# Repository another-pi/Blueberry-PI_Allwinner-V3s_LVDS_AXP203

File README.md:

main build board now is `Blueberry Pi 7.1.2.esp32.no-lan.gsm-a9g`. because `a9g` gsm module is much better then `sim800c`. because of open source SDK and support of GPS.

but still work-in-progress. not finished.

sources of Linux kernel (4.10.15) for this board(s). preconfigured:
https://github.com/bhgv/linux

precompiled Linux-4.10.15 SD-image with support of fb-graphics an resistive touch:
https://github.com/bhgv/linux/releases/tag/1.0a

Blueberry Pi 7.1.2.esp32.no-lan
===============================
(not finished yet)
* removed lan port,
* added 50pins fpc RGB connector for popular 7" tfts (AT070TN[90, 91, 92, 93, 94]) in parallel to 40pins one,
* connector for capacitive touchscreens (i2c1),
* power converters for 50pins socket,
* 25% smaller board.
* esp32 now wired as wifi/bluetooth and as io expander-coprocessor.

Blueberry Pi 7.1.1+ESP32-S
==========================
(not finised yet)
* other power controller(s). 3 cheap and easy to solder chips in sot23-6,
* a try to use ESP32-S module as a WiFi/Bluetooth co-processor.

List of compatible (and cheap) LCDs (with touchscreens)
=======================================================
* ? 7" -- MDT7000
* 7" -- TKR7040B
* 7" -- GL070009T0-40

* 6" -- KD060G1-40nc-a5
* 6" -- TM060RDH02

* 5" -- HSD050IDW1-A20
* 5" -- MH0506D
* 5" -- KD50G21-40NT-A1
* 5" -- A26TF9C032169 * A0 -A20
* 5" -- H-H050L-12M
* 5" -- GL050001C0-40
* 5" -- ft050s800480005n-v01
* 5" -- HW800480F-0F-0L-20
* 5" -- hw800480f-0f-0l-10
* 5" -- T050SWV012T
* 5" -- T050SWV015T
* 5" -- FC050S151-01
* 5" -- KD50G23-40NB-A1
* 5" -- HLY050ML115-12A

(
* 6" -- texet tn-811bt

* 5" --
- Window N5 TOP Tablet PC/ N5PRO/ Onda 580
- TeXet T-939HD
- TeXet T-930HD
- TeXet TN-550A
- TeXet TN-511HD
- TeXet TN-521HD
- TeXet TN-610HD
- TeXet TN-611HD
- TeXet TM-650 (100%)
- Explay PN-955
- Explay PN-960
- SHTURMANN Play 500
- IQU Smile
- Lexand Si-515 Pro HD
- Lexand SG-615 PRO HD
- Ritmix
- EasyGo 500Bi (100%)
- lexand str-5350 hd (100%)
- Prestigio Geovision 5500BTFMHD (100%)
- Prestigio GeoVision 5600GPRSHD
- Explay SLK5
- JXD S5300
- TurboGames New
- EXEQ SET
)

Blueberry Pi 7.1+axp203
=======================
is the Blueberry Pi 7.1 board but with AXP203 power controller, not EA3036. and has DC-DC step down (5-12v) on power input.

Blueberry PI 7.1
================

Added:
------
* LVDS interface with cheap SN65LVDS84 serialiser,
* resistive touchscreen controller TSC2003 + pinheader for resistive touch,
* flash w25q128,
* more popular MicroSD card slot,
* datasheets for them

Removed:
--------
* pinheader for OV7670

Blueberry PI
============
Another fruit single board computer (SBC), based on the Allwinner V3s system on a chip (SOC).
The Allwinner V3s comes in an easy to solder 128pin TQFP package.

The Blueberry PI features:

- 100 mbps Ethernet
- 1 USB Host Port / 1 mini USB port
- MIPI CSI interface (unfortunately no support in the linux kernel yet)
- Pinheader for an OV2640 and an OV7670
- Wifi and bluetooth
- RGB interface for connecting displays
- Audio jack
- an onboard microphone
- four buttons for play, pause, next and previous
- a Raspberry PI compatible header
- SPI Flash
- SD card slot

The Blueberry PI can boot from an SD card or SPI Flash.
Since the V3s doesn't have a standard video output, I'm planning on creating a video addon board which provides VGA or HDMI. In combination with the ADV7611 it is possible to capture HDMI.

If you have any questions email me at marcel[dot]thuermer(at)smail[dot]emt[dot]h[minus]brs[dot]de

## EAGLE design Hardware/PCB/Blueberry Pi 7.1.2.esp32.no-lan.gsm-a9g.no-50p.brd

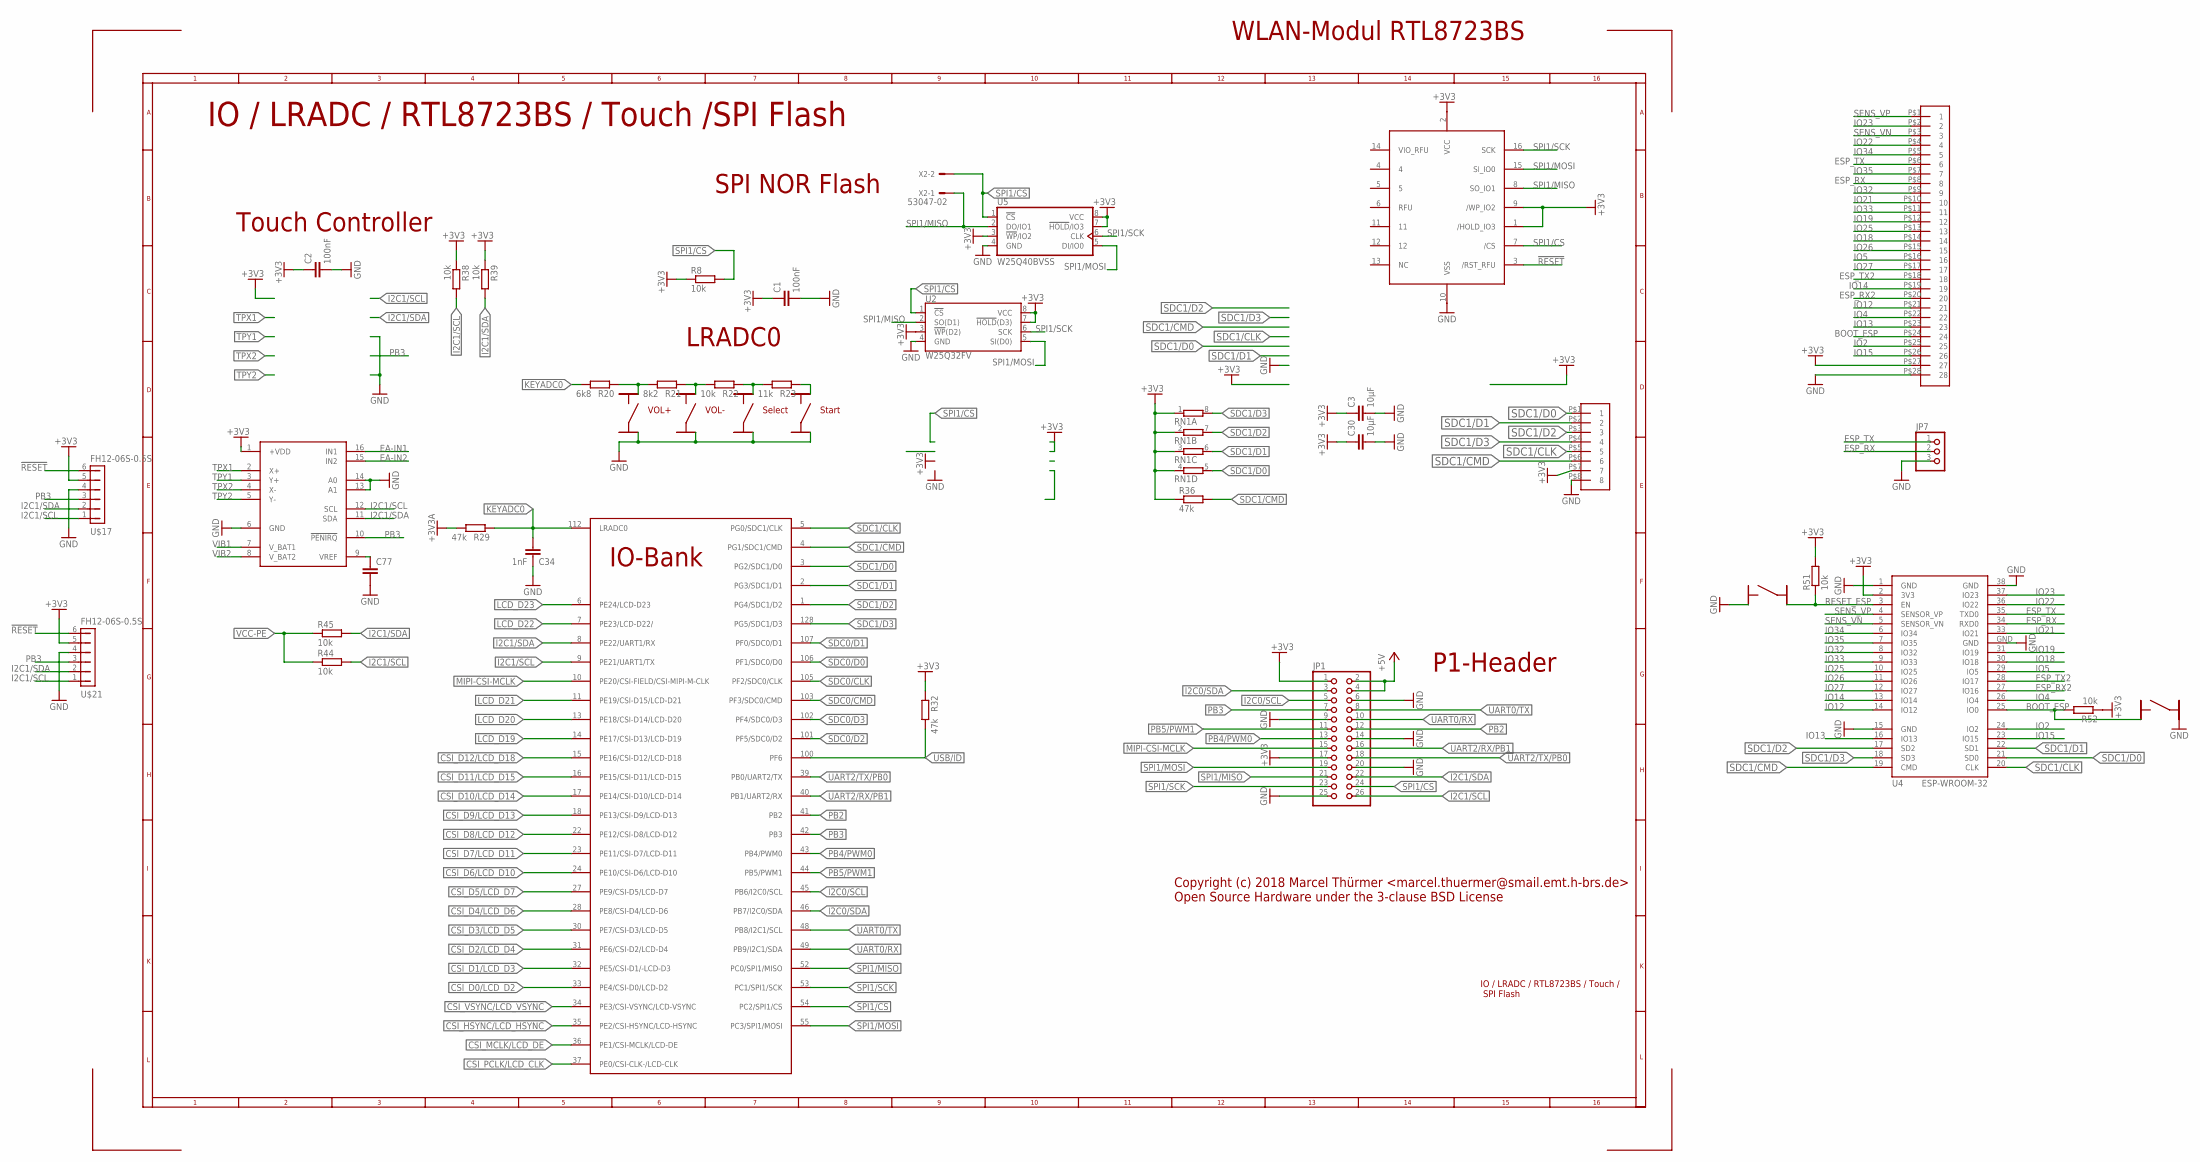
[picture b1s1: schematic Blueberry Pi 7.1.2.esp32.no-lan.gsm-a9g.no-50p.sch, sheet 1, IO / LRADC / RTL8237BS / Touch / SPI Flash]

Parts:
C1, C2: 100nF; C0603
C3, C30: 10µF; C0805
C34: 1nF; C0603
C77: C-EUC0603; C0603
JP1: PINHD-2X13; 2X13
JP7: PINHD-1X3M; 1X03M
R8, R22, R38, R39, R44, R45, R51, R52: 10k; R0603
R20: 6k8; R0603
R21: 8k2; R0603
R23: 11k; R0603
R29, R32, R36: 47k; R0603
RN1: 4R-NEXB38V; EXB38V
S-BOOT-ESP: BUTTON_3X3MM_4PINS; BUT_3X3_4PINS
S-RST-ESP: BUTTON_3X3MM_4PINS; BUT_3X3_4PINS
S-SEL: BUTTON_3X3MM_4PINS; BUT_3X3_4PINS
S-START: BUTTON_3X3MM_4PINS; BUT_3X3_4PINS
S-VOL+: BUTTON_3X3MM_4PINS; BUT_3X3_4PINS
S-VOL-: BUTTON_3X3MM_4PINS; BUT_3X3_4PINS
U2: W25Q32FV; WSON8-6X5MM
U4: ESP-WROOM-32
U5: W25Q40BVSS; SO08-SS
U$1: V3S; QFP-128
U$3: HDR-1.27MM-142; HDR-1.27MM-19*2
U$4: HDR-1.27MM-42; HDR-1.27MM-4*2
U$7: TSC2003; TSSOP16
U$16: S25FL256S; WSOIC-16
U$17, U$21: FH12-06S-0.5S; FH12-6S-0.5SH
X2: 53047-02

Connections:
!RESET: U$16.3 (/RST_RFU), U$17.6, U$21.6; also elsewhere on the board
+3V3: C1.1, C2.1, C3.1, C30.1, JP1.1, JP1.17, R8.1, R32.1, R36.1, R38.1, R39.1, R51.2, R52.1, RN1.1, RN1.2 (1), RN1.3 (1), RN1.4 (1), U2.3 (!WP!(D2)), U2.7 (!HOLD!(D3)), U2.8 (VCC), U4.2 (3V3), U5.3 (!WP!/IO2), U5.7 (!HOLD!/IO3), U5.8 (VCC), U$3.P$27 (27), U$4.P$7 (7), U$7.1 (+VDD), U$16.1 (/HOLD_IO3), U$16.2 (VCC), U$16.9 (/WP_IO2), U$17.5, U$21.5; also elsewhere on the board
+3V3A: R29.2; also elsewhere on the board
+5V: JP1.2, JP1.4; also elsewhere on the board
BOOT_ESP: R52.2, S-BOOT-ESP.P$1, U4.25 (IO0), U$3.P$24 (24)
CSI_D0/LCD_D2: U$1.33 (PE4/CSI-D0/LCD-D2); also elsewhere on the board
CSI_D1/LCD_D3: U$1.32 (PE5/CSI-D1/-LCD-D3); also elsewhere on the board
CSI_D2/LCD_D4: U$1.31 (PE6/CSI-D2/LCD-D4); also elsewhere on the board
CSI_D3/LCD_D5: U$1.30 (PE7/CSI-D3/LCD-D5); also elsewhere on the board
CSI_D4/LCD_D6: U$1.28 (PE8/CSI-D4/LCD-D6); also elsewhere on the board
CSI_D5/LCD_D7: U$1.27 (PE9/CSI-D5/LCD-D7); also elsewhere on the board
CSI_D6/LCD_D10: U$1.24 (PE10/CSI-D6/LCD-D10); also elsewhere on the board
CSI_D7/LCD_D11: U$1.23 (PE11/CSI-D7/LCD-D11); also elsewhere on the board
CSI_D8/LCD_D12: U$1.22 (PE12/CSI-D8/LCD-D12); also elsewhere on the board
CSI_D9/LCD_D13: U$1.18 (PE13/CSI-D9/LCD-D13); also elsewhere on the board
CSI_D10/LCD_D14: U$1.17 (PE14/CSI-D10/LCD-D14); also elsewhere on the board
CSI_D11/LCD_D15: U$1.16 (PE15/CSI-D11/LCD-D15); also elsewhere on the board
CSI_D12/LCD_D18: U$1.15 (PE16/CSI-D12/LCD-D18); also elsewhere on the board
CSI_HSYNC/LCD_HSYNC: U$1.35 (PE2/CSI-HSYNC/LCD-HSYNC); also elsewhere on the board
CSI_MCLK/LCD_DE: U$1.36 (PE1/CSI-MCLK/LCD-DE); also elsewhere on the board
CSI_PCLK/LCD_CLK: U$1.37 (PE0/CSI-CLK-/LCD-CLK); also elsewhere on the board
CSI_VSYNC/LCD_VSYNC: U$1.34 (PE3/CSI-VSYNC/LCD-VSYNC); also elsewhere on the board
EA-IN1: U$7.16 (IN1); also elsewhere on the board
EA-IN2: U$7.15 (IN2); also elsewhere on the board
ESP_RX: JP7.2, U4.34 (RXD0), U$3.P$8 (8)
ESP_RX2: U4.27 (IO16), U$3.P$20 (20); also elsewhere on the board
ESP_TX: JP7.1, U4.35 (TXD0), U$3.P$6 (6)
ESP_TX2: U4.28 (IO17), U$3.P$18 (18); also elsewhere on the board
GND: C1.2, C2.2, C3.2, C30.2, C34.1, C77.2, JP1.6, JP1.9, JP1.14, JP1.20, JP1.25, JP7.3, S-BOOT-ESP.P$2, S-RST-ESP.P$1, S-SEL.P$4, S-START.P$4, S-VOL+.P$4, S-VOL-.P$4, U2.4 (GND), U4.1 (GND), U4.15 (GND), U4.38 (GND), U4.GND, U5.4 (GND), U$3.P$28 (28), U$4.P$8 (8), U$7.6 (GND), U$7.13 (A1), U$7.14 (A0), U$16.10 (VSS), U$17.4, U$21.4; also elsewhere on the board
I2C0/SCL: JP1.5, U$1.45 (PB6/I2C0/SCL)
I2C0/SDA: JP1.3, U$1.46 (PB7/I2C0/SDA)
I2C1/SCL: JP1.26, R38.2, R44.2, U$1.9 (PE21/UART1/TX), U$7.12 (SCL), U$17.1, U$21.1; also elsewhere on the board
I2C1/SDA: JP1.22, R39.2, R45.2, U$1.8 (PE22/UART1/RX), U$7.11 (SDA), U$17.2, U$21.2; also elsewhere on the board
IO2: U4.24 (IO2), U$3.P$25 (25)
IO4: U4.26 (IO4), U$3.P$22 (22)
IO5: U4.29 (IO5), U$3.P$16 (16)
IO12: U4.14 (IO12), U$3.P$21 (21)
IO13: U4.16 (IO13), U$3.P$23 (23)
IO14: U4.13 (IO14), U$3.P$19 (19); also elsewhere on the board
IO15: U4.23 (IO15), U$3.P$26 (26)
IO18: U4.30 (IO18), U$3.P$14 (14)
IO19: U4.31 (IO19), U$3.P$12 (12)
IO21: U4.33 (IO21), U$3.P$10 (10)
IO22: U4.36 (IO22), U$3.P$4 (4)
IO23: U4.37 (IO23), U$3.P$2 (2)
IO25: U4.10 (IO25), U$3.P$13 (13)
IO26: U4.11 (IO26), U$3.P$15 (15)
IO27: U4.12 (IO27), U$3.P$17 (17); also elsewhere on the board
IO32: U4.8 (IO32), U$3.P$9 (9)
IO33: U4.9 (IO33), U$3.P$11 (11)
IO34: U4.6 (IO34), U$3.P$5 (5)
IO35: U4.7 (IO35), U$3.P$7 (7)
KEYADC0: C34.2, R20.2, R29.1, U$1.112 (LRADC0)
LCD_D19: U$1.14 (PE17/CSI-D13/LCD-D19); also elsewhere on the board
LCD_D20: U$1.13 (PE18/CSI-D14/LCD-D20); also elsewhere on the board
LCD_D21: U$1.11 (PE19/CSI-D15/LCD-D21); also elsewhere on the board
LCD_D22: U$1.7 (PE23/LCD-D22/); also elsewhere on the board
LCD_D23: U$1.6 (PE24/LCD-D23); also elsewhere on the board
MIPI-CSI-MCLK: JP1.15, U$1.10 (PE20/CSI-FIELD/CSI-MIPI-M-CLK); also elsewhere on the board
unnamed: R20.1, R21.2, S-VOL+.P$3
unnamed: C77.1, U$7.9 (VREF)
unnamed: R21.1, R22.2, S-VOL-.P$3
unnamed: R22.1, R23.2, S-SEL.P$3
unnamed: R23.1, S-START.P$3
PB2: JP1.12, U$1.41 (PB2); also elsewhere on the board
PB3: JP1.7, U$1.42 (PB3), U$7.10 (!PENIRQ), U$17.3, U$21.3; also elsewhere on the board
PB4/PWM0: JP1.13, U$1.43 (PB4/PWM0); also elsewhere on the board
PB5/PWM1: JP1.11, U$1.44 (PB5/PWM1); also elsewhere on the board
RESET_ESP: R51.1, S-RST-ESP.P$2, U4.3 (EN)
SDC0/CLK: U$1.105 (PF2/SDC0/CLK); also elsewhere on the board
SDC0/CMD: U$1.103 (PF3/SDC0/CMD); also elsewhere on the board
SDC0/D0: U$1.106 (PF1/SDC0/D0); also elsewhere on the board
SDC0/D1: U$1.107 (PF0/SDC0/D1); also elsewhere on the board
SDC0/D2: U$1.101 (PF5/SDC0/D2); also elsewhere on the board
SDC0/D3: U$1.102 (PF4/SDC0/D3); also elsewhere on the board
SDC1/CLK: U4.20 (CLK), U$1.5 (PG0/SDC1/CLK), U$4.P$5 (5)
SDC1/CMD: R36.2, U4.19 (CMD), U$1.4 (PG1/SDC1/CMD), U$4.P$6 (6)
SDC1/D0: RN1.5 (2), U4.21 (SD0), U$1.3 (PG2/SDC1/D0), U$4.P$1 (1)
SDC1/D1: RN1.6 (2), U4.22 (SD1), U$1.2 (PG3/SDC1/D1), U$4.P$2 (2)
SDC1/D2: RN1.7 (2), U4.17 (SD2), U$1.1 (PG4/SDC1/D2), U$4.P$3 (3)
SDC1/D3: RN1.8 (2), U4.18 (SD3), U$1.128 (PG5/SDC1/D3), U$4.P$4 (4)
SENS_VN: U4.5 (SENSOR_VN), U$3.P$3 (3)
SENS_VP: U4.4 (SENSOR_VP), U$3.P$1 (1)
SPI1/CS: JP1.24, R8.2, U2.1 (!CS!), U5.1 (!CS!), U$1.54 (PC2/SPI1/CS), U$16.7 (/CS), X2.2
SPI1/MISO: JP1.21, U2.2 (SO(D1)), U5.2 (DO/IO1), U$1.52 (PC0/SPI1/MISO), U$16.8 (SO_IO1), X2.1
SPI1/MOSI: JP1.19, U2.5 (SI(D0)), U5.5 (DI/IO0), U$1.55 (PC3/SPI1/MOSI), U$16.15 (SI_IO0)
SPI1/SCK: JP1.23, U2.6 (SCK), U5.6 (CLK), U$1.53 (PC1/SPI1/SCK), U$16.16 (SCK)
TPX1: U$7.2 (X+); also elsewhere on the board
TPX2: U$7.4 (X-); also elsewhere on the board
TPY1: U$7.3 (Y+); also elsewhere on the board
TPY2: U$7.5 (Y-); also elsewhere on the board
UART0/RX: JP1.10, U$1.49 (PB9/I2C1/SDA)
UART0/TX: JP1.8, U$1.48 (PB8/I2C1/SCL)
UART2/RX/PB1: JP1.16, U$1.40 (PB1/UART2/RX); also elsewhere on the board
UART2/TX/PB0: JP1.18, U$1.39 (PB0/UART2/TX); also elsewhere on the board
USB/ID: R32.2, U$1.100 (PF6); also elsewhere on the board
VCC-PE: R44.1, R45.1
VIB1: U$7.7 (V_BAT1); also elsewhere on the board
VIB2: U$7.8 (V_BAT2); also elsewhere on the board

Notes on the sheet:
IO / LRADC / RTL8723BS / Touch / SPI Flash
Copyright (c) 2018 Marcel Thürmer <marcel.thuermer@smail.emt.h-brs.de> Open Source Hardware under the 3-clause BSD License
SPI NOR Flash
WLAN-Modul RTL8723BS
P1-Header
LRADC0
Start
Select
VOL-
VOL+
Touch Controller
IO / LRADC / RTL8723BS / Touch /SPI Flash

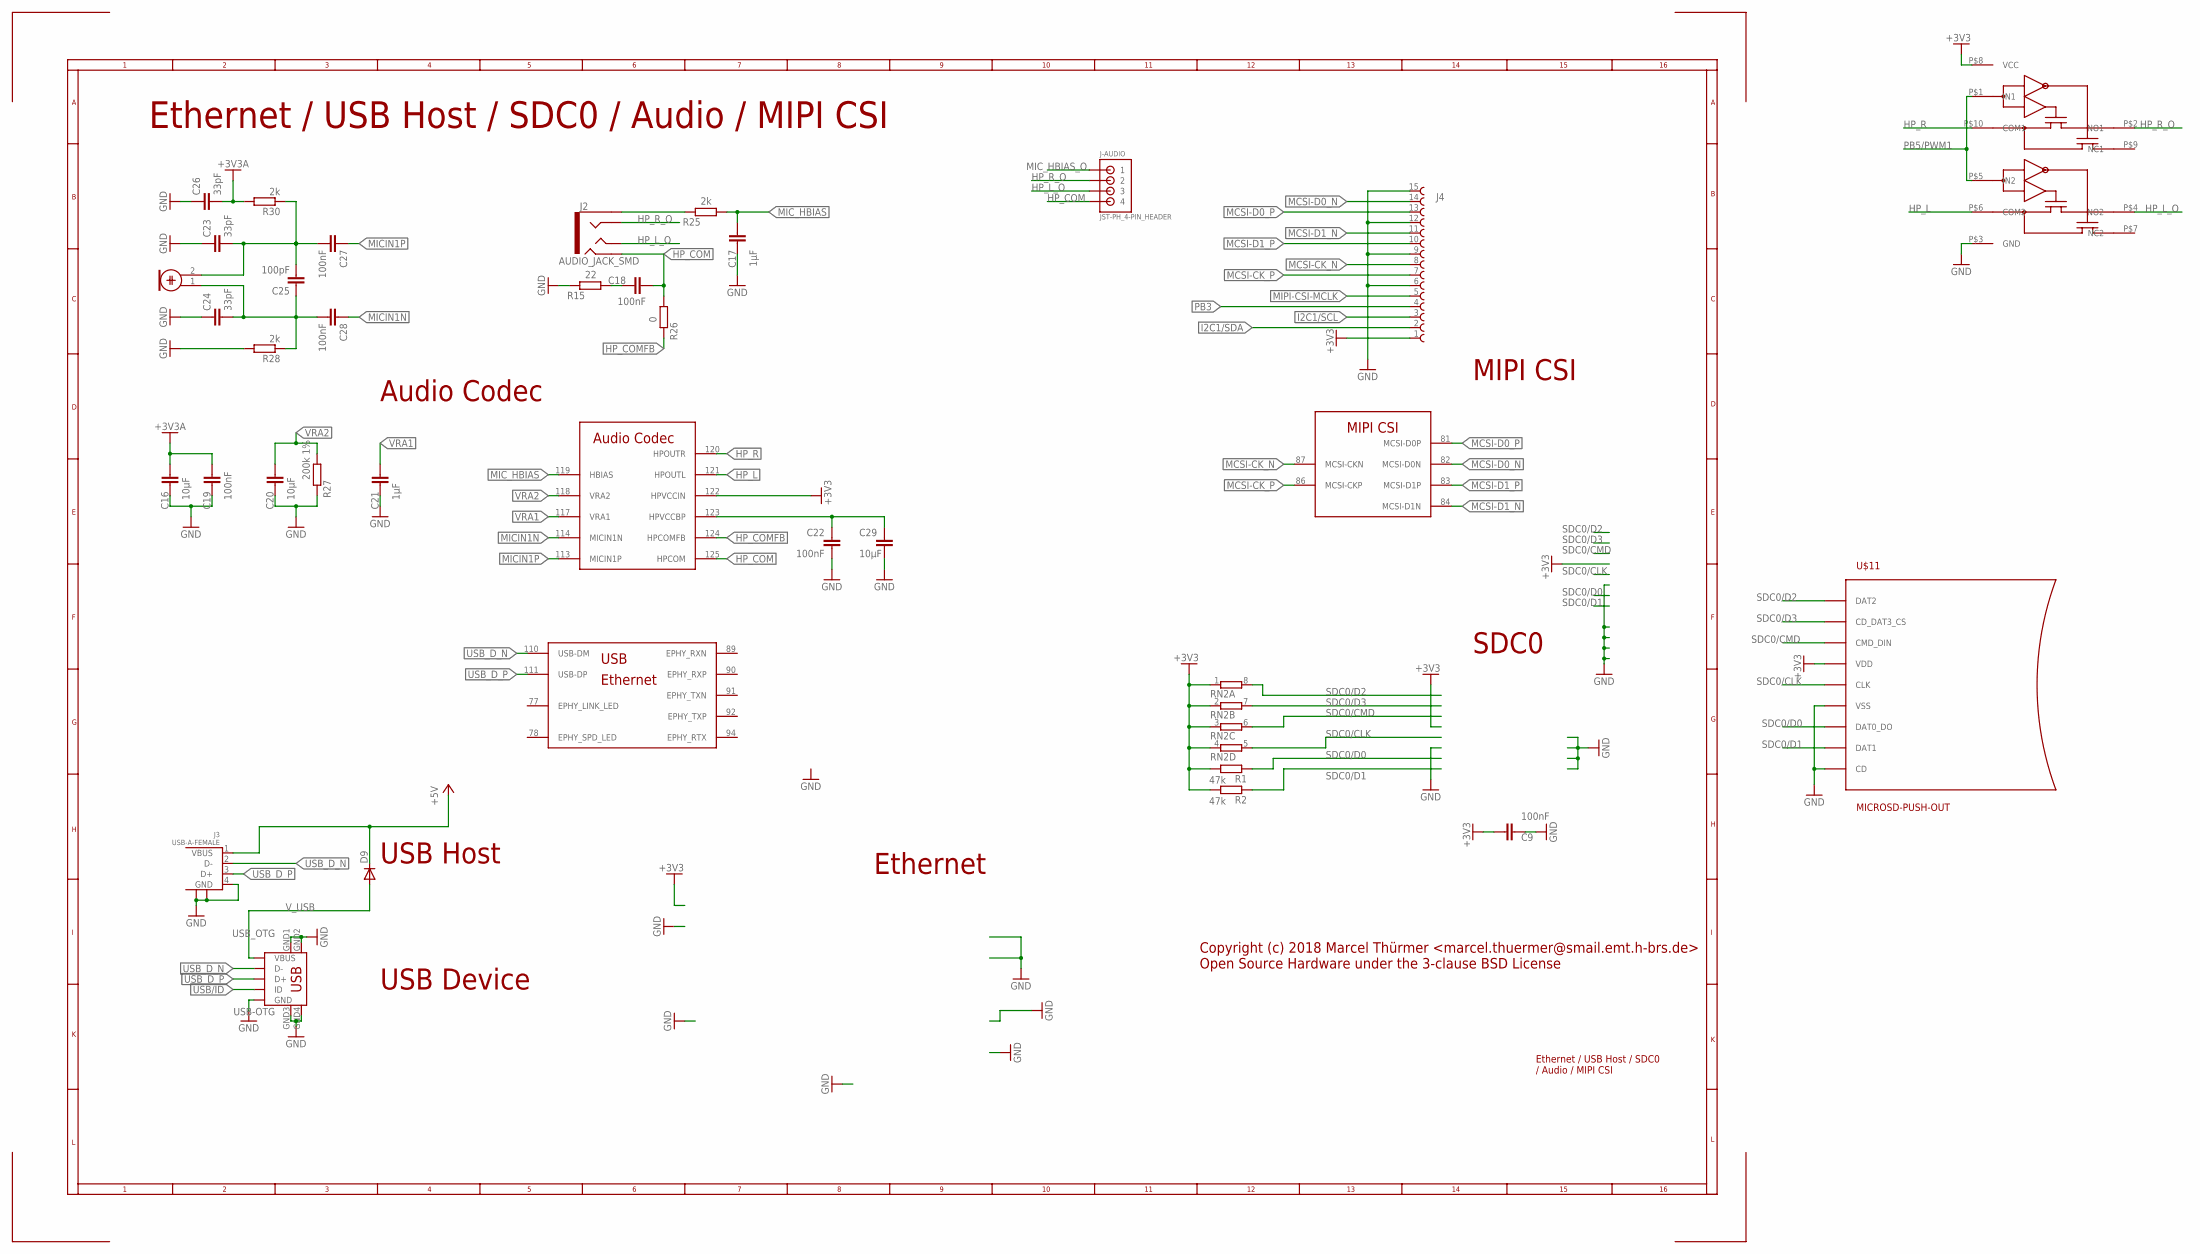
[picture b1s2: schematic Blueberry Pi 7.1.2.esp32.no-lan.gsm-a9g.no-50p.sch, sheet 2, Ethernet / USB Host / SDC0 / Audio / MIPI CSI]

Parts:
C9, C18, C19, C22, C27, C28: 100nF; C0603
C16, C20, C29: 10µF; C0805
C17, C21: 1µF; C0603
C23, C24, C26: 33pF; C0603
C25: 100pF; C0603
D9: DIODE-SOD323-W; SOD323-W
J2: AUDIO_JACK_SMD; AUDIO_JACK_3.5MM_TRRS_SMD_RA
J3: USB-A-FEMALE
J4: 68611514122
J-AUDIO: JST-PH_4-PIN_HEADER; JST_B4B-PH_HEADER
MIC: ELECTRET_MICROPHON-F6035AP; F6035AP
R1, R2: 47k; R0603
R15: 22; R0603
R25, R28, R30: 2k; R0603
R26: 0; R0603
R27: 200k 1%; R0603
RN2: 4R-NEXB38V; EXB38V
U$1: V3S; QFP-128
U$11: MICROSD-PUSH-OUT
U$24: TS5A23157
USB_OTG: USB-OTG; USB_MINI_9PIN

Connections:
+3V3: C9.1, J4.1 (15), R1.2, R2.2, RN2.1, RN2.2 (1), RN2.3 (1), RN2.4 (1), U$1.122 (HPVCCIN), U$11.4 (VDD), U$24.P$8 (VCC); also elsewhere on the board
+3V3A: C16.2, C19.2, C26.2, R30.2; also elsewhere on the board
+5V: D9.C, J3.1 (VBUS); also elsewhere on the board
GND: C9.2, C16.1, C17.2, C19.1, C20.1, C21.1, C22.2, C23.1, C24.1, C26.1, C29.1, J3.4 (GND), J3.P$1, J3.P$2, J4.6 (10), J4.9 (7), J4.12 (4), J4.15 (1), R15.1, R27.1, R28.2, U$11.6 (VSS), U$11.CD, U$11.G1 (VSS), U$11.G2 (VSS), U$11.G3 (VSS), U$11.G4 (VSS), U$24.P$3 (GND), USB_OTG.GND, USB_OTG.GND1, USB_OTG.GND2, USB_OTG.GND3, USB_OTG.GND4; also elsewhere on the board
HP_COM: C18.2, J2.RING2, J-AUDIO.P4 (4), R26.2, U$1.125 (HPCOM)
HP_COMFB: R26.1, U$1.124 (HPCOMFB)
HP_L: U$1.121 (HPOUTL), U$24.P$6 (COM2)
HP_L_O: J2.TIP, J-AUDIO.P3 (3), U$24.P$4 (NO2)
HP_R: U$1.120 (HPOUTR), U$24.P$10 (COM1); also elsewhere on the board
HP_R_O: J2.RING1, J-AUDIO.P2 (2), U$24.P$2 (NO1)
I2C1/SCL: J4.3 (13); also elsewhere on the board
I2C1/SDA: J4.2 (14); also elsewhere on the board
MCSI-CK_N: J4.8, U$1.87 (MCSI-CKN)
MCSI-CK_P: J4.7 (9), U$1.86 (MCSI-CKP)
MCSI-D0_N: J4.14 (2), U$1.82 (MCSI-D0N)
MCSI-D0_P: J4.13 (3), U$1.81 (MCSI-D0P)
MCSI-D1_N: J4.11 (5), U$1.84 (MCSI-D1N)
MCSI-D1_P: J4.10 (6), U$1.83 (MCSI-D1P)
MICIN1N: C28.1, U$1.114 (MICIN1N)
MICIN1P: C27.1, U$1.113 (MICIN1P); also elsewhere on the board
MIC_HBIAS: C17.1, R25.2, U$1.119 (HBIAS)
MIC_HBIAS_O: J2.EARTH, J-AUDIO.P1 (1), R25.1
MIPI-CSI-MCLK: J4.5 (11); also elsewhere on the board
unnamed: C22.1, C29.2, U$1.123 (HPVCCBP)
unnamed: C18.1, R15.2
unnamed: C23.2, C25.2, C27.2, MIC.2, R30.1
unnamed: C24.2, C25.1, C28.2, MIC.1, R28.1
PB3: J4.4 (12); also elsewhere on the board
PB5/PWM1: U$24.P$1 (IN1), U$24.P$5 (IN2); also elsewhere on the board
SDC0/CLK: RN2.5 (2), U$11.5 (CLK); also elsewhere on the board
SDC0/CMD: RN2.6 (2), U$11.3 (CMD_DIN); also elsewhere on the board
SDC0/D0: R1.1, U$11.7 (DAT0_DO); also elsewhere on the board
SDC0/D1: R2.1, U$11.8 (DAT1); also elsewhere on the board
SDC0/D2: RN2.8 (2), U$11.1 (DAT2); also elsewhere on the board
SDC0/D3: RN2.7 (2), U$11.2 (CD_DAT3_CS); also elsewhere on the board
USB/ID: USB_OTG.ID; also elsewhere on the board
USB_D_N: J3.2 (D-), U$1.110 (USB-DM), USB_OTG.D-
USB_D_P: J3.3 (D+), U$1.111 (USB-DP), USB_OTG.D+
VRA1: C21.2, U$1.117 (VRA1)
VRA2: C20.2, R27.2, U$1.118 (VRA2)
V_USB: D9.A, USB_OTG.VBUS; also elsewhere on the board

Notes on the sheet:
Ethernet / USB Host / SDC0 / Audio / MIPI CSI
USB Host
Audio Codec
MIPI CSI
Ethernet
SDC0
Copyright (c) 2018 Marcel Thürmer <marcel.thuermer@smail.emt.h-brs.de> Open Source Hardware under the 3-clause BSD License
USB Device
Ethernet / USB Host / SDC0 / Audio / MIPI CSI

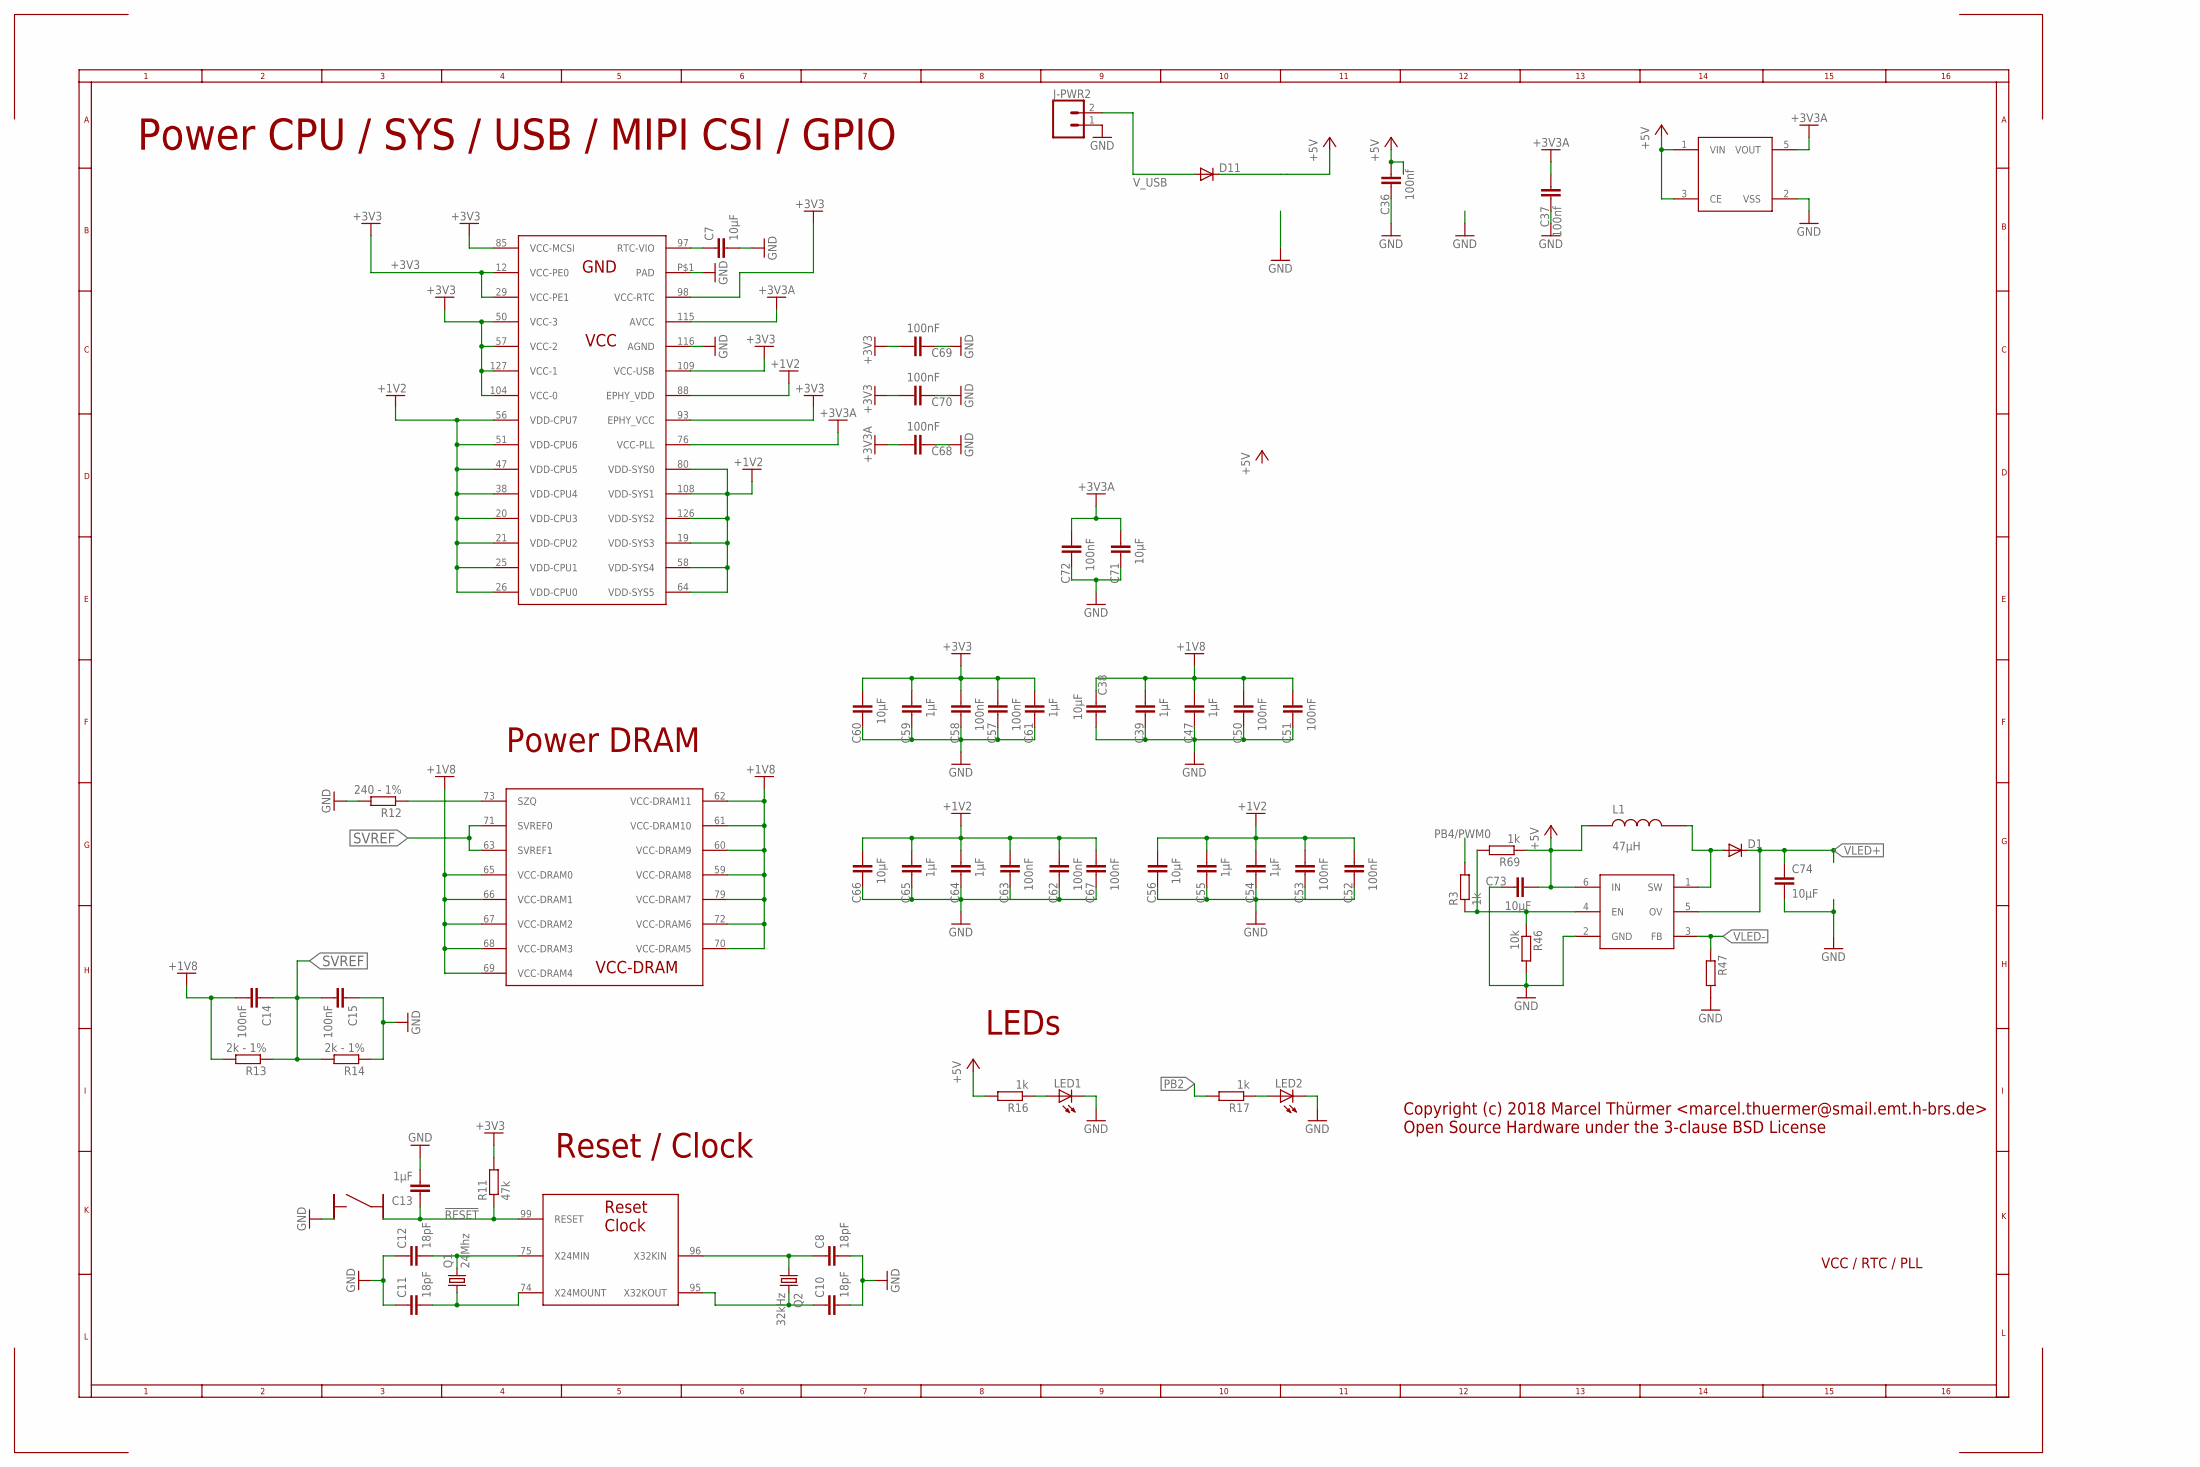
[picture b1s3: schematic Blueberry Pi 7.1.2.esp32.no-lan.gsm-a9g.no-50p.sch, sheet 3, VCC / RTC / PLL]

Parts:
C7, C38, C56, C60, C66, C71, C73, C74: 10µF; C0805
C8, C10, C11, C12: 18pF; C0603
C13, C39, C47, C54, C55, C59, C61, C64, C65: 1µF; C0603
C14, C15, C50, C51, C52, C53, C57, C58, C62, C63, C67, C68, C69, C70, C72: 100nF; C0603
C36, C37: 100nf; C0603
D1, D11: DIODE-SOD323-W; SOD323-W
J-PWR2: CONN_02; 1X02
L1: 47µH; CD32
LED1, LED2: LEDCHIPLED_0805; CHIPLED_0805
Q1: 24Mhz; HC49U-V
Q2: 32kHz; TC38H
R3, R16, R17, R69: 1k; R0603
R11: 47k; R0603
R12: 240 - 1%; R0603
R13, R14: 2k - 1%; R0603
R46: 10k; R0603
R47: R-EU_R0603; R0603
S-RST: BUTTON_3X3MM_4PINS; BUT_3X3_4PINS
U$1: V3S; QFP-128
U$9: PT4101; SOT23-6
U$15: XC6204; SOT25

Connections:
!RESET: C13.1, R11.1, S-RST.P$2, U$1.99 (RESET); also elsewhere on the board
+1V2: C52.1, C53.1, C54.1, C55.1, C56.1, C62.1, C63.1, C64.1, C65.1, C66.1, C67.1, U$1.19 (VDD-SYS3), U$1.20 (VDD-CPU3), U$1.21 (VDD-CPU2), U$1.25 (VDD-CPU1), U$1.26 (VDD-CPU0), U$1.38 (VDD-CPU4), U$1.47 (VDD-CPU5), U$1.51 (VDD-CPU6), U$1.56 (VDD-CPU7), U$1.58 (VDD-SYS4), U$1.64 (VDD-SYS5), U$1.80 (VDD-SYS0), U$1.88 (EPHY_VDD), U$1.108 (VDD-SYS1), U$1.126 (VDD-SYS2); also elsewhere on the board
+1V8: C14.2, C38.2, C39.1, C47.1, C50.1, C51.1, R13.2, U$1.59 (VCC-DRAM8), U$1.60 (VCC-DRAM9), U$1.61 (VCC-DRAM10), U$1.62 (VCC-DRAM11), U$1.65 (VCC-DRAM0), U$1.66 (VCC-DRAM1), U$1.67 (VCC-DRAM2), U$1.68 (VCC-DRAM3), U$1.69 (VCC-DRAM4), U$1.70 (VCC-DRAM5), U$1.72 (VCC-DRAM6), U$1.79 (VCC-DRAM7); also elsewhere on the board
+3V3: C57.1, C58.1, C59.1, C60.1, C61.1, C69.1, C70.1, R11.2, U$1.12 (VCC-PE0), U$1.29 (VCC-PE1), U$1.50 (VCC-3), U$1.57 (VCC-2), U$1.85 (VCC-MCSI), U$1.93 (EPHY_VCC), U$1.98 (VCC-RTC), U$1.104 (VCC-0), U$1.109 (VCC-USB), U$1.127 (VCC-1); also elsewhere on the board
+3V3A: C37.1, C68.1, C71.1, C72.1, U$1.76 (VCC-PLL), U$1.115 (AVCC), U$15.5 (VOUT); also elsewhere on the board
+5V: C36.1, C73.1, D11.C, L1.P$1, R16.2, R69.1, U$9.6 (IN), U$15.1 (VIN), U$15.3 (CE); also elsewhere on the board
GND: C7.2, C8.2, C10.2, C11.1, C12.1, C13.2, C15.1, C36.2, C37.2, C38.1, C39.2, C47.2, C50.2, C51.2, C52.2, C53.2, C54.2, C55.2, C56.2, C57.2, C58.2, C59.2, C60.2, C61.2, C62.2, C63.2, C64.2, C65.2, C66.2, C67.2, C68.2, C69.2, C70.2, C71.2, C72.2, C73.2, C74.2, J-PWR2.1, LED1.C, LED2.C, R12.2, R14.1, R46.2, R47.2, S-RST.P$1, U$1.116 (AGND), U$1.P$1 (PAD), U$9.2 (GND), U$15.2 (VSS); also elsewhere on the board
unnamed: LED1.A, R16.1
unnamed: LED2.A, R17.1
unnamed: R3.1, R46.1, R69.2, U$9.4 (EN)
unnamed: D1.A, L1.P$2, U$9.1 (SW)
unnamed: C7.1, U$1.97 (RTC-VIO)
unnamed: C10.1, Q2.2, U$1.95 (X32KOUT)
unnamed: C8.1, Q2.1, U$1.96 (X32KIN)
unnamed: C11.2, Q1.1, U$1.74 (X24MOUNT)
unnamed: C12.2, Q1.2, U$1.75 (X24MIN)
unnamed: R12.1, U$1.73 (SZQ)
PB2: R17.2; also elsewhere on the board
PB4/PWM0: R3.2; also elsewhere on the board
SVREF: C14.1, C15.2, R13.1, R14.2, U$1.63 (SVREF1), U$1.71 (SVREF0)
VLED+: C74.1, D1.C, U$9.5 (OV); also elsewhere on the board
VLED-: R47.1, U$9.3 (FB); also elsewhere on the board
V_USB: D11.A, J-PWR2.2; also elsewhere on the board

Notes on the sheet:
VCC / RTC / PLL
Power CPU / SYS / USB / MIPI CSI / GPIO
Power DRAM
Copyright (c) 2018 Marcel Thürmer <marcel.thuermer@smail.emt.h-brs.de> Open Source Hardware under the 3-clause BSD License
Reset / Clock
LEDs

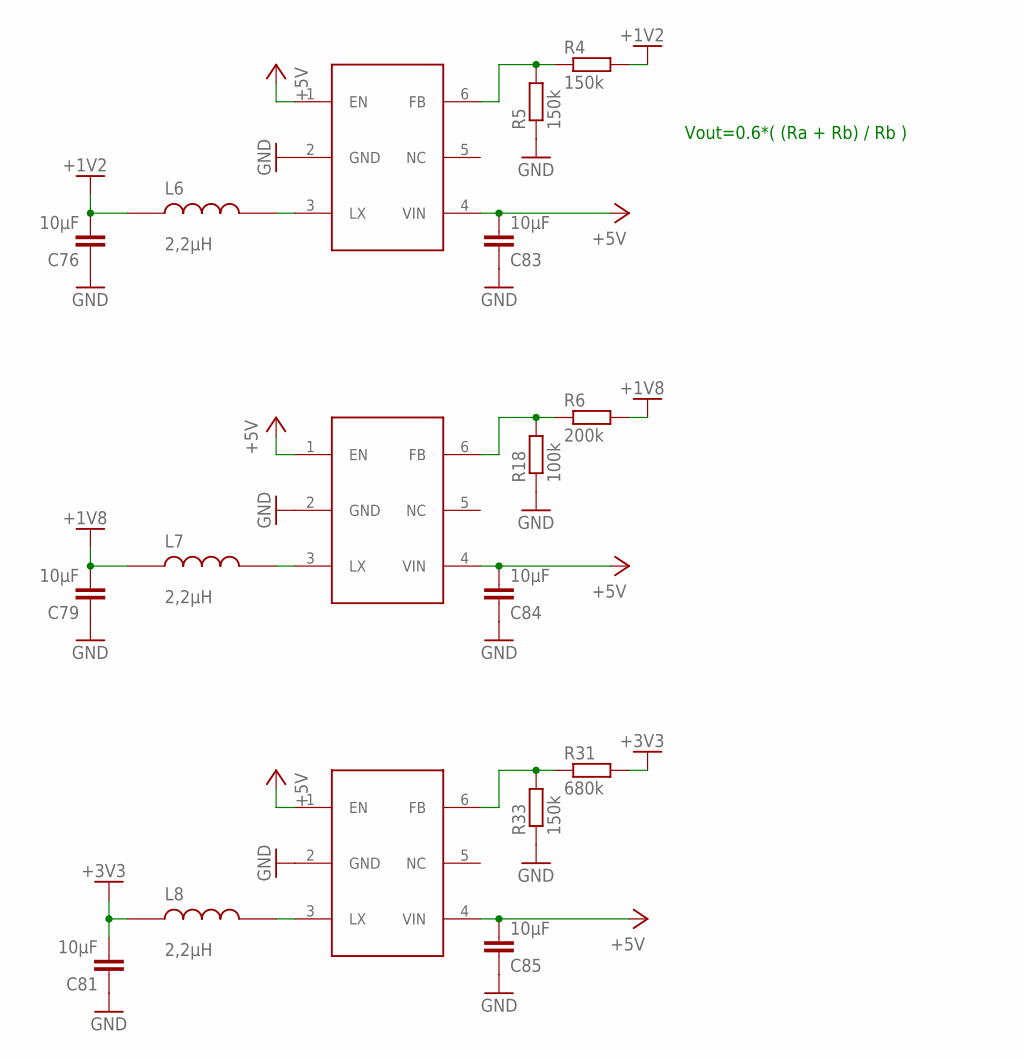
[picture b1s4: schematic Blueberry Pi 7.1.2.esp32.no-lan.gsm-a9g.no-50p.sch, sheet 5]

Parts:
C76, C79, C81, C83, C84, C85: 10µF; C0805
L6, L7, L8: 2,2µH; CD32
R4, R5, R33: 150k; R0603
R6: 200k; R0603
R18: 100k; R0603
R31: 680k; R0603
U$5, U$12, U$13: STI3411; SOT23-6

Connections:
+1V2: C76.2, L6.P$1, R4.2; also elsewhere on the board
+1V8: C79.2, L7.P$1, R6.2; also elsewhere on the board
+3V3: C81.2, L8.P$1, R31.2; also elsewhere on the board
+5V: C83.2, C84.2, C85.2, U$5.1 (EN), U$5.4 (VIN), U$12.1 (EN), U$12.4 (VIN), U$13.1 (EN), U$13.4 (VIN); also elsewhere on the board
GND: C76.1, C79.1, C81.1, C83.1, C84.1, C85.1, R5.1, R18.1, R33.1, U$5.2 (GND), U$12.2 (GND), U$13.2 (GND); also elsewhere on the board
unnamed: L6.P$2, U$13.3 (LX)
unnamed: L7.P$2, U$5.3 (LX)
unnamed: R4.1, R5.2, U$13.6 (FB)
unnamed: L8.P$2, U$12.3 (LX)
unnamed: R6.1, R18.2, U$5.6 (FB)
unnamed: R31.1, R33.2, U$12.6 (FB)

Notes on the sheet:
Vout=0.6*( (Ra + Rb) / Rb )

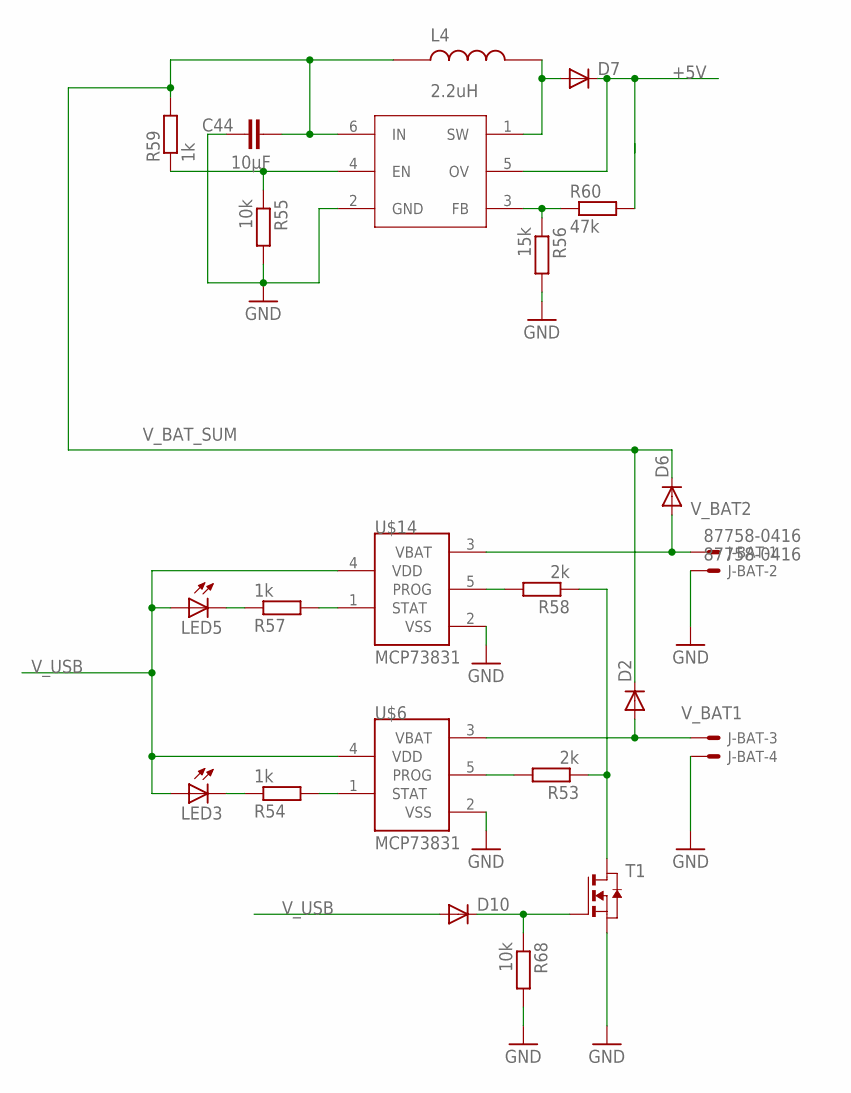
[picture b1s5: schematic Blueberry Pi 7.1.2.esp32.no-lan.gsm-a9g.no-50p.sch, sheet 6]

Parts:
C44: 10µF; C0805
D2, D6: DIODE-DO214AC; DO214AC
D7, D10: DIODE-SOD323-W; SOD323-W
J-BAT: 87758-0416
L4: 2.2uH; CD32
LED3, LED5: LEDCHIPLED_0805; CHIPLED_0805
R53, R58: 2k; R0603
R54, R57, R59: 1k; R0603
R55, R68: 10k; R0603
R56: 15k; R0603
R60: 47k; R0603
T1: NMOSSOT23; SOT-23
U$6, U$14: MCP73831; SOT23-5L
U$10: PT4101; SOT23-6

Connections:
+5V: D7.C, R60.2, U$10.5 (OV); also elsewhere on the board
GND: C44.2, J-BAT.2, J-BAT.4, R55.2, R56.2, R68.2, T1.2 (S), U$6.2 (VSS), U$10.2 (GND), U$14.2 (VSS); also elsewhere on the board
unnamed: R53.1, R58.1, T1.1 (D)
unnamed: R56.1, R60.1, U$10.3 (FB)
unnamed: R55.1, R59.1, U$10.4 (EN)
unnamed: D7.A, L4.P$2, U$10.1 (SW)
unnamed: D10.C, R68.1, T1.3 (G)
unnamed: R53.2, U$6.5 (PROG)
unnamed: LED3.C, R54.1
unnamed: R54.2, U$6.1 (STAT)
unnamed: R58.2, U$14.5 (PROG)
unnamed: R57.2, U$14.1 (STAT)
unnamed: LED5.C, R57.1
V_BAT1: D2.A, J-BAT.3, U$6.3 (VBAT)
V_BAT2: D6.A, J-BAT.1, U$14.3 (VBAT)
V_BAT_SUM: C44.1, D2.C, D6.C, L4.P$1, R59.2, U$10.6 (IN); also elsewhere on the board
V_USB: D10.A, LED3.A, LED5.A, U$6.4 (VDD), U$14.4 (VDD); also elsewhere on the board

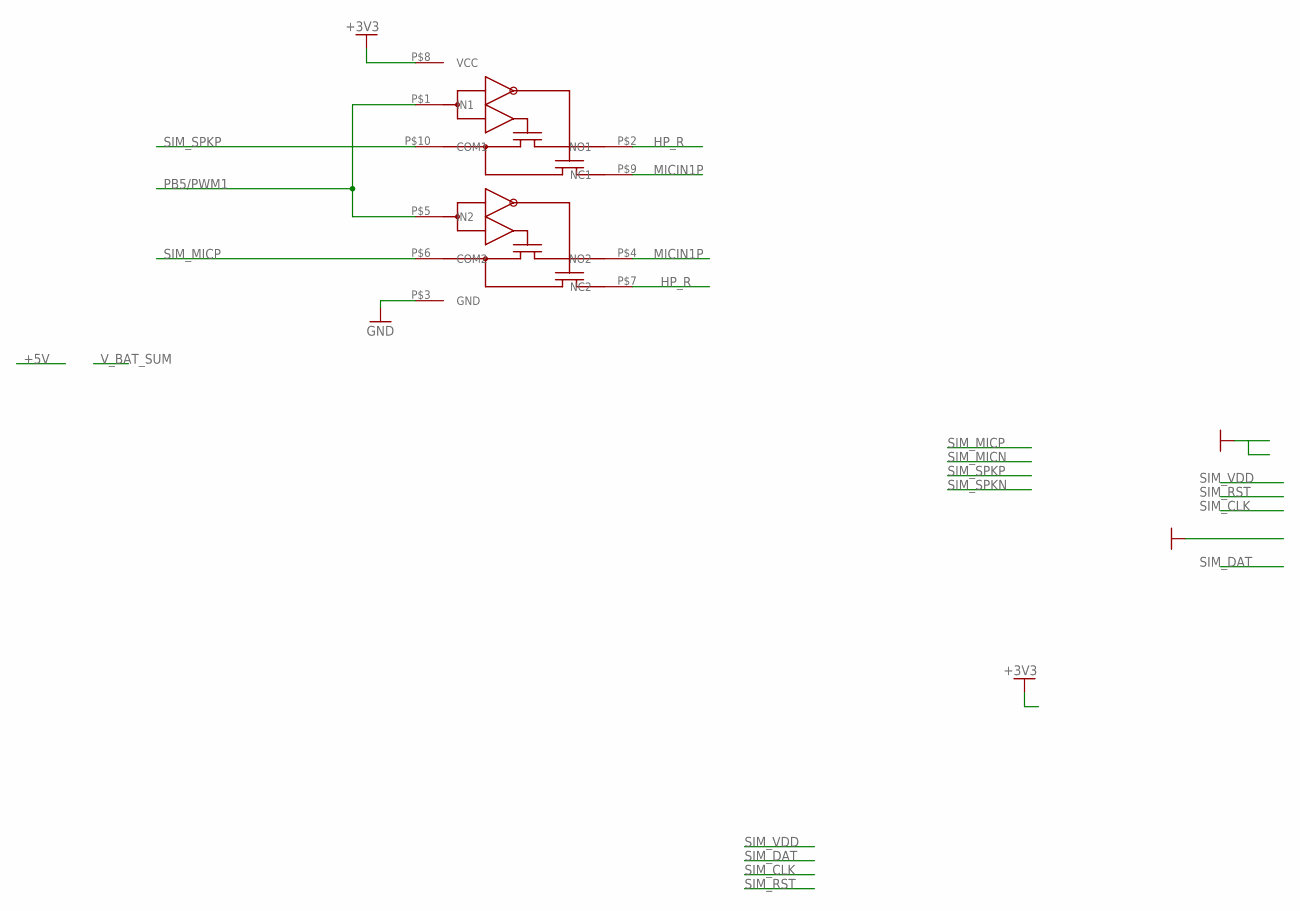
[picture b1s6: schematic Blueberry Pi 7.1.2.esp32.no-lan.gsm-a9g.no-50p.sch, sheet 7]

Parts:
U$19: TS5A23157

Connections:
+3V3: U$19.P$8 (VCC); also elsewhere on the board
GND: U$19.P$3 (GND); also elsewhere on the board
HP_R: U$19.P$2 (NO1), U$19.P$7 (NC2); also elsewhere on the board
MICIN1P: U$19.P$4 (NO2), U$19.P$9 (NC1); also elsewhere on the board
PB5/PWM1: U$19.P$1 (IN1), U$19.P$5 (IN2); also elsewhere on the board
SIM_MICP: U$19.P$6 (COM2); also elsewhere on the board
SIM_SPKP: U$19.P$10 (COM1); also elsewhere on the board

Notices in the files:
parts and their libraries:
SparkFun-Connectors: Licensing: Creative Commons ShareAlike 4.0 International - https://creativecommons.org/licenses/by-sa/4.0
EAGLE-FPC_CONNECTOR_AND_FFC_CAB-rev16b: Copyright: Würth Elektronik
esp32-1: Creative Commons Attribution-ShareAlike 4.0 International
